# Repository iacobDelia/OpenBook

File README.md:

# Bill of Materials
| Componenta    | Link | Datasheet
| -------- | ------- |--------|
| ESP32_WROVER_EAGLE-LTSPICE_RR0402  | https://www.snapeda.com/parts/RC0402FR-07226RL/Yageo/view-part/    |https://www.snapeda.com/parts/RC0402FR-07226RL/Yageo/datasheet/
| QWIIC_CONNECTORJS-1MM | https://www.snapeda.com/parts/PRT-14417/SparkFun/view-part/     |https://www.snapeda.com/parts/PRT-14417/SparkFun%20Electronics/datasheet/
|BUTTON_CUSYOMV1|https://industry.panasonic.com/global/en/downloads?tab=cad&small_g_cd=203&part_no=EVQPUJ02K&q=RVZRUFVKMDJLJTdDMTMlN0MyMDMlN0MzNDU5JTdDMSU3QyU3QyU3Q2ZhbHNl|https://industry.panasonic.com/global/en/downloads?tab=catalog&small_g_cd=203&part_no=EVQPUJ02K&q=RVZRUFVKMDJLJTdDMTMlN0MyMDMlN0MzNDU5JTdDMSU3QyU3QzIlN0NmYWxzZQ%3D%3D
|ESP32_WROVER_EAGLE-LTSPICE_CC0402|https://componentsearchengine.com/part-view/CC0402MRX5R5BB106/YAGEO|https://componentsearchengine.com/Datasheets/2/CC0402MRX5R5BB106.pdf
|CPH3225A|https://www.snapeda.com/parts/CPH3225A/Seiko+Instruments/view-part/?ref=eda|https://www.snapeda.com/parts/CPH3225A/Seiko%20Instruments/datasheet/|
|ADAFRUIT_LEDCHIP-LED0603|https://www.snapeda.com/parts/KP-1608SURCK/Kingbright/view-part/?ref=search&t=LED%200603|https://www.snapeda.com/parts/KP-1608SURCK/Kingbright/datasheet/
|112A-TAAR-R03_ATTEND|https://store.comet.bg/en/Catalogue/Product/43497/|https://store.comet.bg/en/Catalogue/Product/43497/|
|744043680IND_4828-WE-TPC_WRE|https://www.digikey.sg/en/models/1638515|https://www.we-online.com/components/products/datasheet/744043680.pdf
|BD5229G-TR|https://componentsearchengine.com/part-view/BD5229G-TR/ROHM%20Semiconductor|https://datasheet.datasheetarchive.com/originals/distributors/Datasheets_SAMA/f2b9741ef86007909f138d561a359946.pdf|
|CPH3225A|https://www.snapeda.com/parts/CPH3225A/Seiko+Instruments/view-part/?ref=eda|https://www.snapeda.com/parts/CPH3225A/Seiko%20Instruments/datasheet/|
|DS3231SN|https://www.snapeda.com/parts/DS3231SN%23/Analog+Devices/view-part/?ref=eda|https://www.snapeda.com/parts/DS3231SN%23/Analog%20Devices/datasheet/|
|ESP32-C6-WROOM-1-N8|https://www.snapeda.com/parts/ESP32-C6-WROOM-1-N8/Espressif+Systems/view-part/?ref=eda|https://www.snapeda.com/parts/ESP32-C6-WROOM-1-N8/Espressif%20Systems/datasheet/
|MCP73831|https://www.digikey.com/en/models/1874108|https://ww1.microchip.com/downloads/aemDocuments/documents/APID/ProductDocuments/DataSheets/MCP73831-Family-Data-Sheet-DS20001984H.pdf|
|ESP32_WROVER_BME680_BME680|https://www.snapeda.com/parts/BME680/Bosch/view-part/?welcome=home|https://www.snapeda.com/parts/BME680/Bosch%20Sensortec/datasheet/|
|ESP32_WROVER_EAGLE-LTSPICE_CC0402|https://componentsearchengine.com/Datasheets/2/CC0402MRX5R5BB106.pdf|https://componentsearchengine.com/part-view/CC0402MRX5R5BB106/YAGEO|
|ESP32_WROVER_SPARKFUN-DISCRETESEMI_MOSFET_PCH-DMG2305UX-7|https://componentsearchengine.com/part-view/DMG2305UX-7/Diodes%20Incorporated|https://www.diodes.com//assets/Datasheets/DMG2305UX.pdf|
|ESP32C6_VARISTORCN1812|https://www.mouser.co.uk/ProductDetail/EPCOS-TDK/B72520T0350K062?qs=dEfas%2FXlABIszF52uu7vrg%3D%3D|https://www.tdk-electronics.tdk.com/inf/75/db/CTVS_14/Surge_protection_series.pdf|
|FH34SRJ-24S-0.5SH_99_|https://componentsearchengine.com/part-view/XC6220A331MR-G/Torex|https://product.torexsemi.com/system/files/series/xc6220.pdf|
|MAX17048G+T10|https://www.snapeda.com/parts/MAX17048G+T10/Analog+Devices/view-part/?ref=eda|https://www.snapeda.com/parts/MAX17048G+T10/Analog%20Devices/datasheet/|
|MBR0530|https://ro.mouser.com/ProductDetail/KYOCERA-AVX/SD0805S020S1R0?qs=jCA%252BPfw4LHbpkAoSnwrdjw%3D%3D|https://ro.mouser.com/datasheet/2/40/schottky-3165252.pdf|
|PGB1010603MR|https://www.snapeda.com/parts/PGB1010603MR/Littelfuse/view-part/?ref=eda|https://www.snapeda.com/parts/PGB1010603MR/Littelfuse%20Inc./datasheet/|
|RCL_CPOL-EUCT3528|https://ro.mouser.com/ProductDetail/Vishay-Sprague/TR3B106K025C1300?qs=jCGqFXxTmLdffnuDkXzk1g%3D%3D|https://www.vishay.com/docs/40080/tr3.pdf|
|SAMACSYS_PARTS_USB4110-GF-A|https://componentsearchengine.com/part-view/USB4110-GF-A/GCT%20(GLOBAL%20CONNECTOR%20TECHNOLOGY)|https://gct.co/files/drawings/usb4110.pdf|
|SI1308EDL-T1-GE3|https://componentsearchengine.com/part-view/SI1308EDL-T1-GE3/Vishay|https://componentsearchengine.com/Datasheets/1/SI1308EDL-T1-GE3.pdf|
|SJ|https://grabcad.com/library/solder-jumpers-1||
|USBLC6-2SC6Y|https://www.snapeda.com/parts/USBLC6-2SC6Y/STMicroelectronics/view-part/?ref=eda|https://www.snapeda.com/parts/USBLC6-2SC6Y/STMicroelectronics/datasheet/|
|W25Q512JVEIQ|https://www.snapeda.com/parts/W25Q512JVEIQ/Winbond+Electronics/view-part/?ref=eda|https://www.snapeda.com/parts/W25Q512JVEIQ/Winbond%20Electronics/datasheet/|
|XC6220A331MR-G|https://componentsearchengine.com/part-view/XC6220A331MR-G/Torex|https://product.torexsemi.com/system/files/series/xc6220.pdf|

# Functionalitati Hardware
## Microcontroller
Microcontroller principal: ESP32-C6-WROOM-1-N8

    Interfețe: UART, I²C, SPI, GPIO, ADC, PWM, USB 2.0

    Comunicare wireless: WiFi 6 (802.11ax), Bluetooth 5.0 Low Energy, Zigbee & Thread (prin IEEE 802.15.4)

    Memorie: 8 MB Flash

    Rol: Controler central ce gestionează comunicația cu toate perifericele și modulele externe. Este responsabil pentru achiziția de date, procesare și trimiterea lor către o interfață (de ex. server sau aplicație mobilă).

Ceas în timp real: DS3231SN

    Tip: RTC (Real-Time Clock) cu compensare termică

    Interfață: I²C

    Rol: Asigură măsurarea precisă a timpului, util pentru timestamp-ul datelor colectate de senzori.

Senzor de mediu: BME680

    Măsoară: Temperatură, presiune, umiditate și compuși organici volatili (VOC)

    Interfață: I²C (poate fi și SPI)

    Rol: Oferă date esențiale de mediu pentru aplicații IoT, monitorizare atmosferică etc.

### Managementul energiei
MCP73831

    Rol: Încărcător Li-Ion / Li-Po

    Interfață: Analogică, configurabilă prin rezistențe externe

    Caracteristici: Control al curentului de încărcare, protecții integrate

MAX17048G+T10

    Rol: Fuel Gauge IC

    Interfață: I²C

    Funcții: Măsoară tensiunea și estimează nivelul bateriei (SoC - state of charge)

Memorie externă: W25Q512JVEIQ

    Tip: NOR Flash, 512Mbit

    Interfață: SPI

    Rol: Stocare de date (loguri, configurări, firmware OTA)

Protecție și integritate electrică

    USBLC6-2SC6Y – Protecție ESD pentru liniile USB

    PGB1010603MR – Protecție împotriva descărcărilor electrostatice (ESD)

    SI1308EDL-T1-GE3 / DMG2305UX-7 – MOSFET pentru comutarea energiei sau protecție

    BD5229G-TR – Regulator LDO de 2.9V

    Varistor CN1812 (B72520T0350K062) – Protecție la supratensiuni

    Diodă Schottky (MBR0530) – Prevenirea curenților inversi

Conectivitate externă

    QWIIC_CONNECTORJS-1MM – Conector pentru I²C (QWIIC standard, modular, plug-and-play)

    SAMACSYS_PARTS_USB4110-GF-A – USB-C pentru alimentare și comunicare

    112A-TAAR-R03_ATTEND – Conector placă-la-placă

    SJ (Solder Jumpers) – Permite configurarea opțională a traseelor prin punți de lipit

Feedback vizual & control

    ADAFRUIT_LEDCHIP-LED0603 (KP-1608SURCK) – LED de status

    BUTTON_CUSYOMV1 (EVQPUJ02K) – Buton mecanic, folosit pentru reset, input de utilizator sau inițierea unei funcții

# Total consum
Componentă|	Consum tipic|
|-------|----------|
|ESP32-C6|	~130mA |
|BME680|	~3.1µA (low power)|	
|DS3231SN|	~200nA	|
|MAX17048|	~23µA	|
|MCP73831|	până la 500mA|	
|LED-uri|	~2-10mA	|

Total estimativ în mod activ: ~150-180mA

## Conexiuni componente la pini ESP32-C6
RTC – DS3231SN

    Interfață: I²C

    Pini ESP32-C6 folosiți:

        GPIO8 – I²C SDA

        GPIO9 – I²C SCL

    Motiv: GPIO8 și GPIO9 sunt frecvent utilizați pentru magistrala I²C pe ESP32-C6 deoarece pot fi configurate software și sunt ușor de accesat. SDA și SCL trebuie trase cu rezistențe de pull-up (tipic 4.7kΩ).

Senzor mediu – BME680

    Interfață: I²C (partajează magistrala cu DS3231)

    Pini ESP32-C6 folosiți:

        GPIO8 – SDA

        GPIO9 – SCL

    Motiv: Magistrala I²C permite conectarea în paralel a mai multor dispozitive, fiecare având adresă unică.

Fuel Gauge – MAX17048

    Interfață: I²C

    Pini: Aceeași magistrală I²C (GPIO8 & GPIO9)

    Motiv: MAX17048 are adresă I²C fixă, deci trebuie verificat să nu fie conflict cu celelalte două componente (nu e cazul aici).

Memorie externă – W25Q512JVEIQ

    Interfață: SPI

    Pini ESP32-C6:

        GPIO4 – SPI MOSI

        GPIO5 – SPI MISO

        GPIO6 – SPI CLK

        GPIO7 – SPI CS

    Motiv: Aceste GPIO-uri sunt pinii SPI hardware dedicați pe ESP32-C6 și asigură performanță maximă și compatibilitate cu interfața SPI (QSPI în cazul memoriei).

LED (KP-1608SURCK)

    Interfață: GPIO (digital out, cu rezistor în serie)

    Pin:

        GPIO3 – LED Control

    Motiv: GPIO3 este un pin liber cu capabilități PWM, ceea ce permite și control al intensității (dimming), nu doar on/off.

Buton (EVQPUJ02K)

    Interfață: GPIO + Pull-up intern

    Pin:

        GPIO0 – Buton utilizator

    Motiv: GPIO0 este adesea folosit și pentru bootloader/reset (cu atenție la stări în timpul pornirii). E un pin convenabil pentru input digital.

Qwiic Connector (I²C extensibil)

    Pini: I²C SDA/SCL partajați

        GPIO8 – SDA

        GPIO9 – SCL

    Motiv: Qwiic folosește același protocol I²C, deci toate dispozitivele compatibile Qwiic se pot lega în paralel la acești pini.

MCP73831 – Încărcare baterie

    Pini:

        VBUS / USB – Alimentare 5V

        STAT pin legat la GPIO10 (monitorizare charging status)

    Motiv: GPIO10 este configurabil ca input pentru a citi starea de încărcare (LED status al MCP73831 conectat la pinul STAT).

MAX17048 – Fuel Gauge

    Alimentare + I²C (vezi mai sus)

    INT (optional): Conectat la GPIO1

    Motiv: GPIO1 poate fi configurat cu întrerupere (interrupt) pentru notificări despre nivelul bateriei critic/scăzut.

USB4110-GF-A – USB-C connector

    Funcție: Alimentare 5V și comunicație

    Pin USB D+ / D- conectați la:

        GPIO18 – USB D+

        GPIO19 – USB D-

    Motiv: ESP32-C6 are suport USB nativ. Aceste GPIO-uri sunt default pentru perifericul USB Device.

Alte conexiuni:

    CPH3225A (oscilator 32.768 kHz) – utilizat pentru RTC, conectat la pinul dedicat RTC_CLKIN (sau la DS3231 dacă nu e folosit direct de MCU)

    MOSFET & diodă Schottky – control și protecție, comutarea pinilor GPIO pentru pornire/oprire module

    Varistor, rezistențe, condensatori – pasive pentru protecție, filtrare și stabilitate electrică (nu folosesc GPIO-uri direct)

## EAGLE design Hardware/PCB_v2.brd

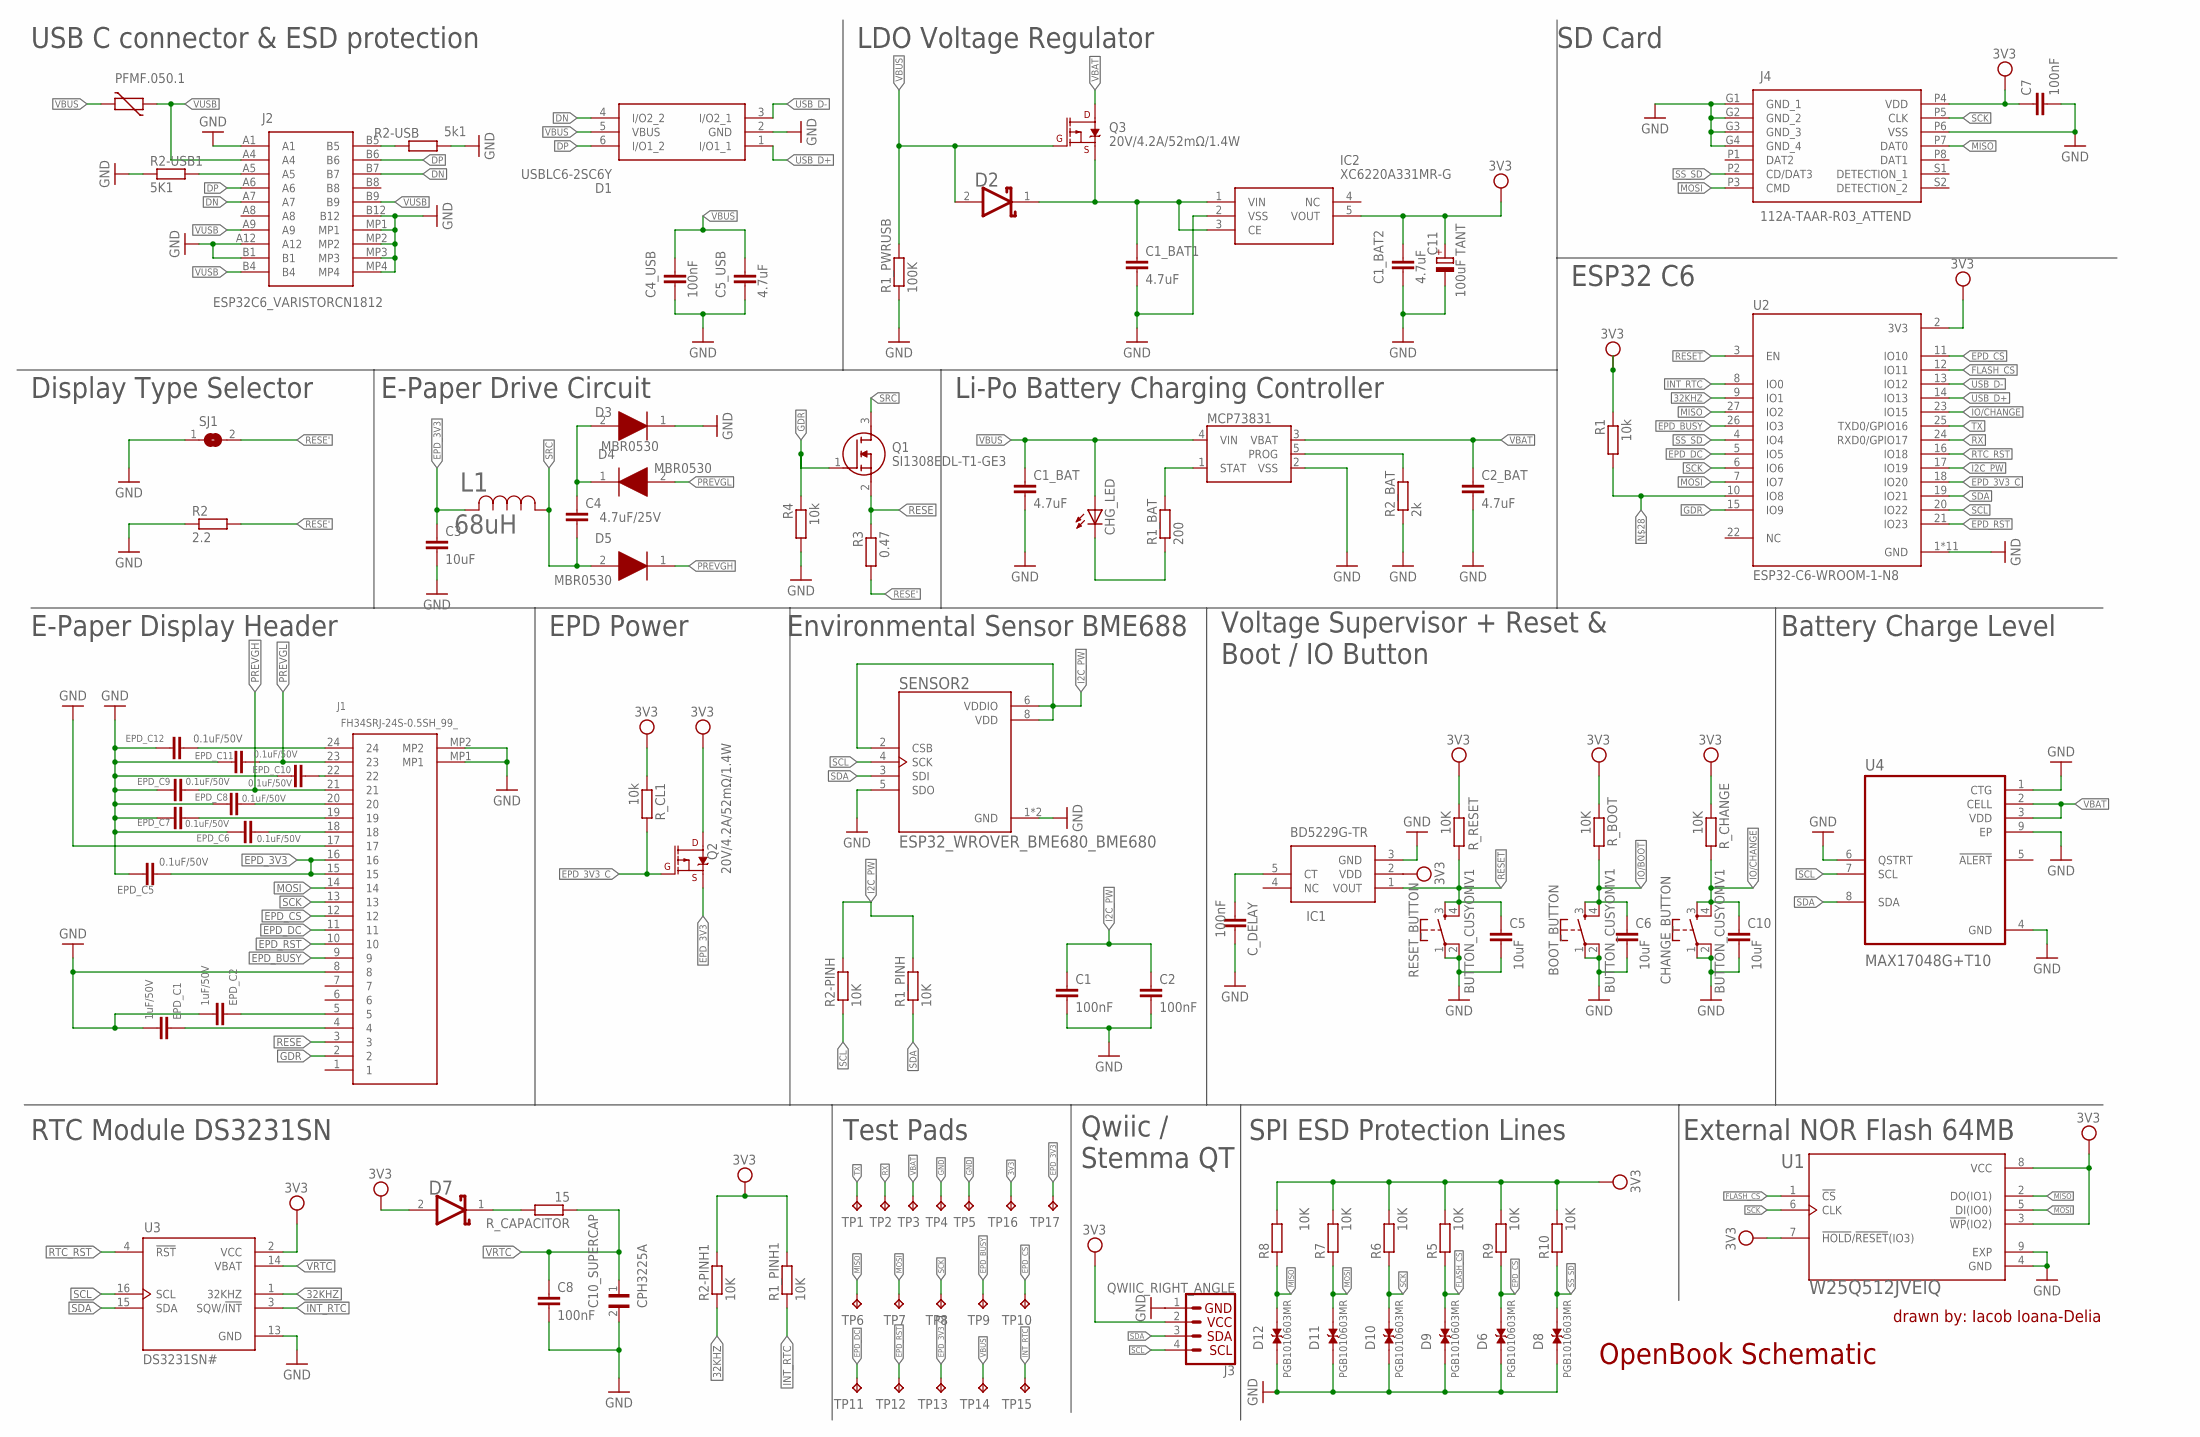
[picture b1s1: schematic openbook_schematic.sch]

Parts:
BOOT_BUTTON: BUTTON_CUSYOMV1; MYBUTTON
C1, C2, C4_USB, C7, C8: 100nF; ESP32_WROVER_EAGLE-LTSPICE_C0402
C1_BAT, C1_BAT1, C1_BAT2, C2_BAT, C5_USB: 4.7uF; ESP32_WROVER_EAGLE-LTSPICE_C0402
C3, C5, C6, C10: 10uF; ESP32_WROVER_EAGLE-LTSPICE_C0402
C4: 4.7uF/25V; ESP32_WROVER_EAGLE-LTSPICE_C0402
C10_SUPERCAP: CPH3225A; CAPCP3225X100N
C11: 100uF TANT; RCL_CT3528
CHANGE_BUTTON: BUTTON_CUSYOMV1; MYBUTTON
CHG_LED: ADAFRUIT_LEDCHIP-LED0603; ADAFRUIT_CHIP-LED0603
C_DELAY: 100nF; ESP32_WROVER_EAGLE-LTSPICE_C0402
D1: USBLC6-2SC6Y; SOT95P280X145-6N
D2, D7: ESP32_WROVER_AVX---SD0805S020S1R0_AVX_SD0805S020S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; ESP32_WROVER_AVX---SD0805S020S1R0_AVX_SD0805S020S1R0_0
D3, D4, D5: MBR0530; SOD3716X135N
D6, D8, D9, D10, D11, D12: PGB1010603MR; DIOC1608X36N
EPD_C1, EPD_C2: 1uF/50V; ESP32_WROVER_EAGLE-LTSPICE_C0402
EPD_C5, EPD_C6, EPD_C7, EPD_C8, EPD_C9, EPD_C10, EPD_C11, EPD_C12: 0.1uF/50V; ESP32_WROVER_EAGLE-LTSPICE_C0402
IC1: BD5229G-TR; SOT95P280X125-5N
IC2: XC6220A331MR-G; SOT95P280X120-5N
J1: FH34SRJ-24S-0.5SH_99_; FH34SRJ24S05SH99
J2: SAMACSYS_PARTS_USB4110-GF-A; SAMACSYS_PARTS_USB4110GFA
J3: QWIIC_RIGHT_ANGLE; JST04_1MM_RA
J4: 112A-TAAR-R03_ATTEND; 112ATAARR03ATTEND
L1: 68uH; IND_4828-WE-TPC_WRE
MCP73831: ESP32_WROVER_SPARKFUN-IC-POWER_MCP73831; ESP32_WROVER_SPARKFUN-IC-POWER_SOT23-5
PFMF.050.1: ESP32C6_VARISTORCN1812; ESP32C6_VARISTOR_CT/CN1812
Q1: SI1308EDL-T1-GE3; SOT65P210X110-3N
Q2, Q3: 20V/4.2A/52mΩ/1.4W; ESP32_WROVER_SPARKFUN-DISCRETESEMI_SOT23-3
R1, R4: 10k; ESP32_WROVER_EAGLE-LTSPICE_R0402
R1_BAT: 200; ESP32_WROVER_EAGLE-LTSPICE_R0402
R1_PINH, R1_PINH1, R2-PINH, R2-PINH1, R5, R6, R7, R8, R9, R10: 10K; ESP32_WROVER_EAGLE-LTSPICE_R0402
R1_PWRUSB: 100K; ESP32_WROVER_EAGLE-LTSPICE_R0402
R2: 2.2; ESP32_WROVER_EAGLE-LTSPICE_R0402
R2-USB: 5k1; ESP32_WROVER_EAGLE-LTSPICE_R0402
R2-USB1: 5K1; ESP32_WROVER_EAGLE-LTSPICE_R0402
R2_BAT: 2k; ESP32_WROVER_EAGLE-LTSPICE_R0402
R3: 0.47; ESP32_WROVER_EAGLE-LTSPICE_R0402
RESET_BUTTON: BUTTON_CUSYOMV1; MYBUTTON
R_BOOT: 10K; ESP32_WROVER_EAGLE-LTSPICE_R0402
R_CAPACITOR: 15; ESP32_WROVER_EAGLE-LTSPICE_R0402
R_CHANGE: 10K; ESP32_WROVER_EAGLE-LTSPICE_R0402
R_CL1: 10k; ESP32_WROVER_EAGLE-LTSPICE_R0402
R_RESET: 10K; ESP32_WROVER_EAGLE-LTSPICE_R0402
SENSOR2: ESP32_WROVER_BME680_BME680; ESP32_WROVER_BME680_PSON80P300X300X100-8N
SJ1: SJ
TP1, TP2, TP3, TP4, TP5, TP6, TP7, TP8, TP9, TP10, TP11, TP12, TP13, TP14, TP15, TP16, TP17: TPTP20R; TP20R
U1: W25Q512JVEIQ; SON127P600X800X80-9N
U2: ESP32-C6-WROOM-1-N8; XCVR_ESP32-C6-WROOM-1-N8
U3: DS3231SN#; SOIC127P1032X265-16N
U4: MAX17048G+T10; SON50P200X200X80-9N

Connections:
3V3: C1_BAT2.1, C7.1, C11.+, D7.2 (ANODE), IC1.2 (VDD), IC2.5 (VOUT), J3.2, J4.P4 (VDD), Q2.3 (D), R1.1, R1_PINH1.2, R2-PINH1.2, R5.2, R6.2, R7.2, R8.2, R9.2, R10.2, R_BOOT.1, R_CHANGE.1, R_CL1.1, R_RESET.1, TP16.TP, U1.3 (!WP!(IO2)), U1.7 (!HOLD!/!RESET!(IO3)), U1.8 (VCC), U2.2 (3V3), U3.2 (VCC)
32KHZ: R2-PINH1.1, U2.9 (IO1), U3.1 (32KHZ)
DN: D1.4 (I/O2_2), J2.A7, J2.B7
DP: D1.6 (I/O1_2), J2.A6, J2.B6
EPD_3V3: C3.1, EPD_C5.1, J1.15, J1.16, L1.2, Q2.2 (S), TP17.TP
EPD_3V3_C: Q2.1 (G), R_CL1.2, TP13.TP, U2.18 (IO20)
EPD_BUSY: J1.9, TP9.TP, U2.26 (IO3)
EPD_CS: D6.2, J1.12, R9.1, TP10.TP, U2.11 (IO10)
EPD_DC: J1.11, TP11.TP, U2.5 (IO5)
EPD_RST: J1.10, TP12.TP, U2.21 (IO23)
FLASH_CS: D9.2, R5.1, U1.1 (!CS), U2.12 (IO11)
GND: BOOT_BUTTON.1, BOOT_BUTTON.2, C1.2, C1_BAT.2, C1_BAT1.2, C1_BAT2.2, C2.2, C2_BAT.2, C3.2, C4_USB.2, C5.2, C5_USB.2, C6.2, C7.2, C8.2, C10.2, C10_SUPERCAP.2, C11.-, CHANGE_BUTTON.1, CHANGE_BUTTON.2, C_DELAY.2, D1.2 (GND), D3.1 (K), D6.1, D8.1, D9.1, D10.1, D11.1, D12.1, EPD_C1.2, EPD_C2.2, EPD_C5.2, EPD_C6.2, EPD_C7.2, EPD_C8.2, EPD_C9.2, EPD_C10.2, EPD_C11.2, EPD_C12.2, IC1.3 (GND), IC2.2 (VSS), J1.8, J1.17, J1.MP1, J1.MP2, J2.A1, J2.A12, J2.B1, J2.B12, J2.MP1, J2.MP2, J2.MP3, J2.MP4, J3.1, J4.G1 (GND_1), J4.G2 (GND_2), J4.G3 (GND_3), J4.G4 (GND_4), J4.P6 (VSS), MCP73831.2 (VSS), R1_PWRUSB.1, R2.1, R2-USB.2, R2-USB1.1, R2_BAT.1, R4.2, RESET_BUTTON.1, RESET_BUTTON.2, SENSOR2.1 (GND), SENSOR2.5 (SDO), SENSOR2.7 (GND), SJ1.1, TP4.TP, TP5.TP, U1.4 (GND), U1.9 (EXP), U2.1 (GND), U2.28 (GND), U2.29_1 (GND), U2.29_2 (GND), U2.29_3 (GND), U2.29_4 (GND), U2.29_5 (GND), U2.29_6 (GND), U2.29_7 (GND), U2.29_8 (GND), U2.29_9 (GND), U3.13 (GND), U4.1 (CTG), U4.4 (GND), U4.6 (QSTRT), U4.9 (EP)
I2C_PW: C1.1, C2.1, R1_PINH.2, R2-PINH.2, SENSOR2.2 (CSB), SENSOR2.6 (VDDIO), SENSOR2.8 (VDD), U2.17 (IO19)
INT_RTC: R1_PINH1.1, TP15.TP, U2.8 (IO0), U3.3 (SQW/!INT)
IO/CHANGE: C10.1, CHANGE_BUTTON.3, CHANGE_BUTTON.4, R_CHANGE.2, U2.23 (IO15)
MISO: D12.2, J4.P7 (DAT0), R8.1, TP6.TP, U1.2 (DO(IO1)), U2.27 (IO2)
MOSI: D11.2, J1.14, J4.P3 (CMD), R7.1, TP7.TP, U1.5 (DI(IO0)), U2.7 (IO7)
unnamed: EPD_C1.1, J1.4
unnamed: EPD_C2.1, J1.5
unnamed: D7.1 (CATHODE), R_CAPACITOR.2
unnamed: EPD_C6.1, J1.18
unnamed: EPD_C7.1, J1.19
unnamed: EPD_C8.1, J1.20
unnamed: C_DELAY.1, IC1.5 (CT)
unnamed: EPD_C10.1, J1.22
unnamed: C4.1, D3.2 (A), D4.1 (K)
unnamed: EPD_C12.1, J1.24
unnamed: J2.B5, R2-USB.1
unnamed: MCP73831.1 (STAT), R1_BAT.2
unnamed: CHG_LED.C, R1_BAT.1
unnamed: MCP73831.5 (PROG), R2_BAT.2
unnamed: C1_BAT1.1, D2.1 (CATHODE), IC2.1 (VIN), IC2.3 (CE), Q3.2 (S)
unnamed: J2.A5, R2-USB1.2
PREVGH: D5.1 (K), EPD_C9.1, J1.21
PREVGL: D4.2 (A), EPD_C11.1, J1.23
RESE: J1.3, Q1.2 (S), R3.1
RESE': R2.2, R3.2, SJ1.2
RESET: C5.1, IC1.1 (VOUT), RESET_BUTTON.3, RESET_BUTTON.4, R_RESET.2, U2.3 (EN)
RTC_RST: U2.16 (IO18), U3.4 (!RST)
RX: TP2.TP, U2.24 (RXD0/GPIO17)
SCK: D10.2, J1.13, J4.P5 (CLK), R6.1, TP8.TP, U1.6 (CLK), U2.6 (IO6)
SCL: J3.4, R2-PINH.1, SENSOR2.4 (SCK), U2.20 (IO22), U3.16 (SCL), U4.7 (SCL)
SDA: J3.3, R1_PINH.1, SENSOR2.3 (SDI), U2.19 (IO21), U3.15 (SDA), U4.8 (SDA)
SRC: C4.2, D5.2 (A), L1.1, Q1.3 (D)
SS_SD: D8.2, J4.P2 (CD/DAT3), R10.1, U2.4 (IO4)
TX: TP1.TP, U2.25 (TXD0/GPIO16)
USB_D+: D1.1 (I/O1_1), U2.14 (IO13)
USB_D-: D1.3 (I/O2_1), U2.13 (IO12)
VBAT: C2_BAT.1, MCP73831.3 (VBAT), Q3.3 (D), TP3.TP, U4.2 (CELL), U4.3 (VDD)
VBUS: C1_BAT.1, C4_USB.1, C5_USB.1, CHG_LED.A, D1.5 (VBUS), D2.2 (ANODE), MCP73831.4 (VIN), PFMF.050.1.2, Q3.1 (G), R1_PWRUSB.2, TP14.TP
VRTC: C8.1, C10_SUPERCAP.1, R_CAPACITOR.1, U3.14 (VBAT)
VUSB: J2.A4, J2.A9, J2.B4, J2.B9, PFMF.050.1.1

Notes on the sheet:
E-Paper Display Header
RTC Module DS3231SN
Test Pads
Qwiic / Stemma QT
SPI ESD Protection Lines
External NOR Flash 64MB
Battery Charge Level
Voltage Supervisor + Reset & Boot / IO Button
Environmental Sensor BME688
EPD Power
Display Type Selector
E-Paper Drive Circuit
Li-Po Battery Charging Controller
ESP32 C6
SD Card
LDO Voltage Regulator
USB C connector & ESD protection
OpenBook Schematic
drawn by: Iacob Ioana-Delia

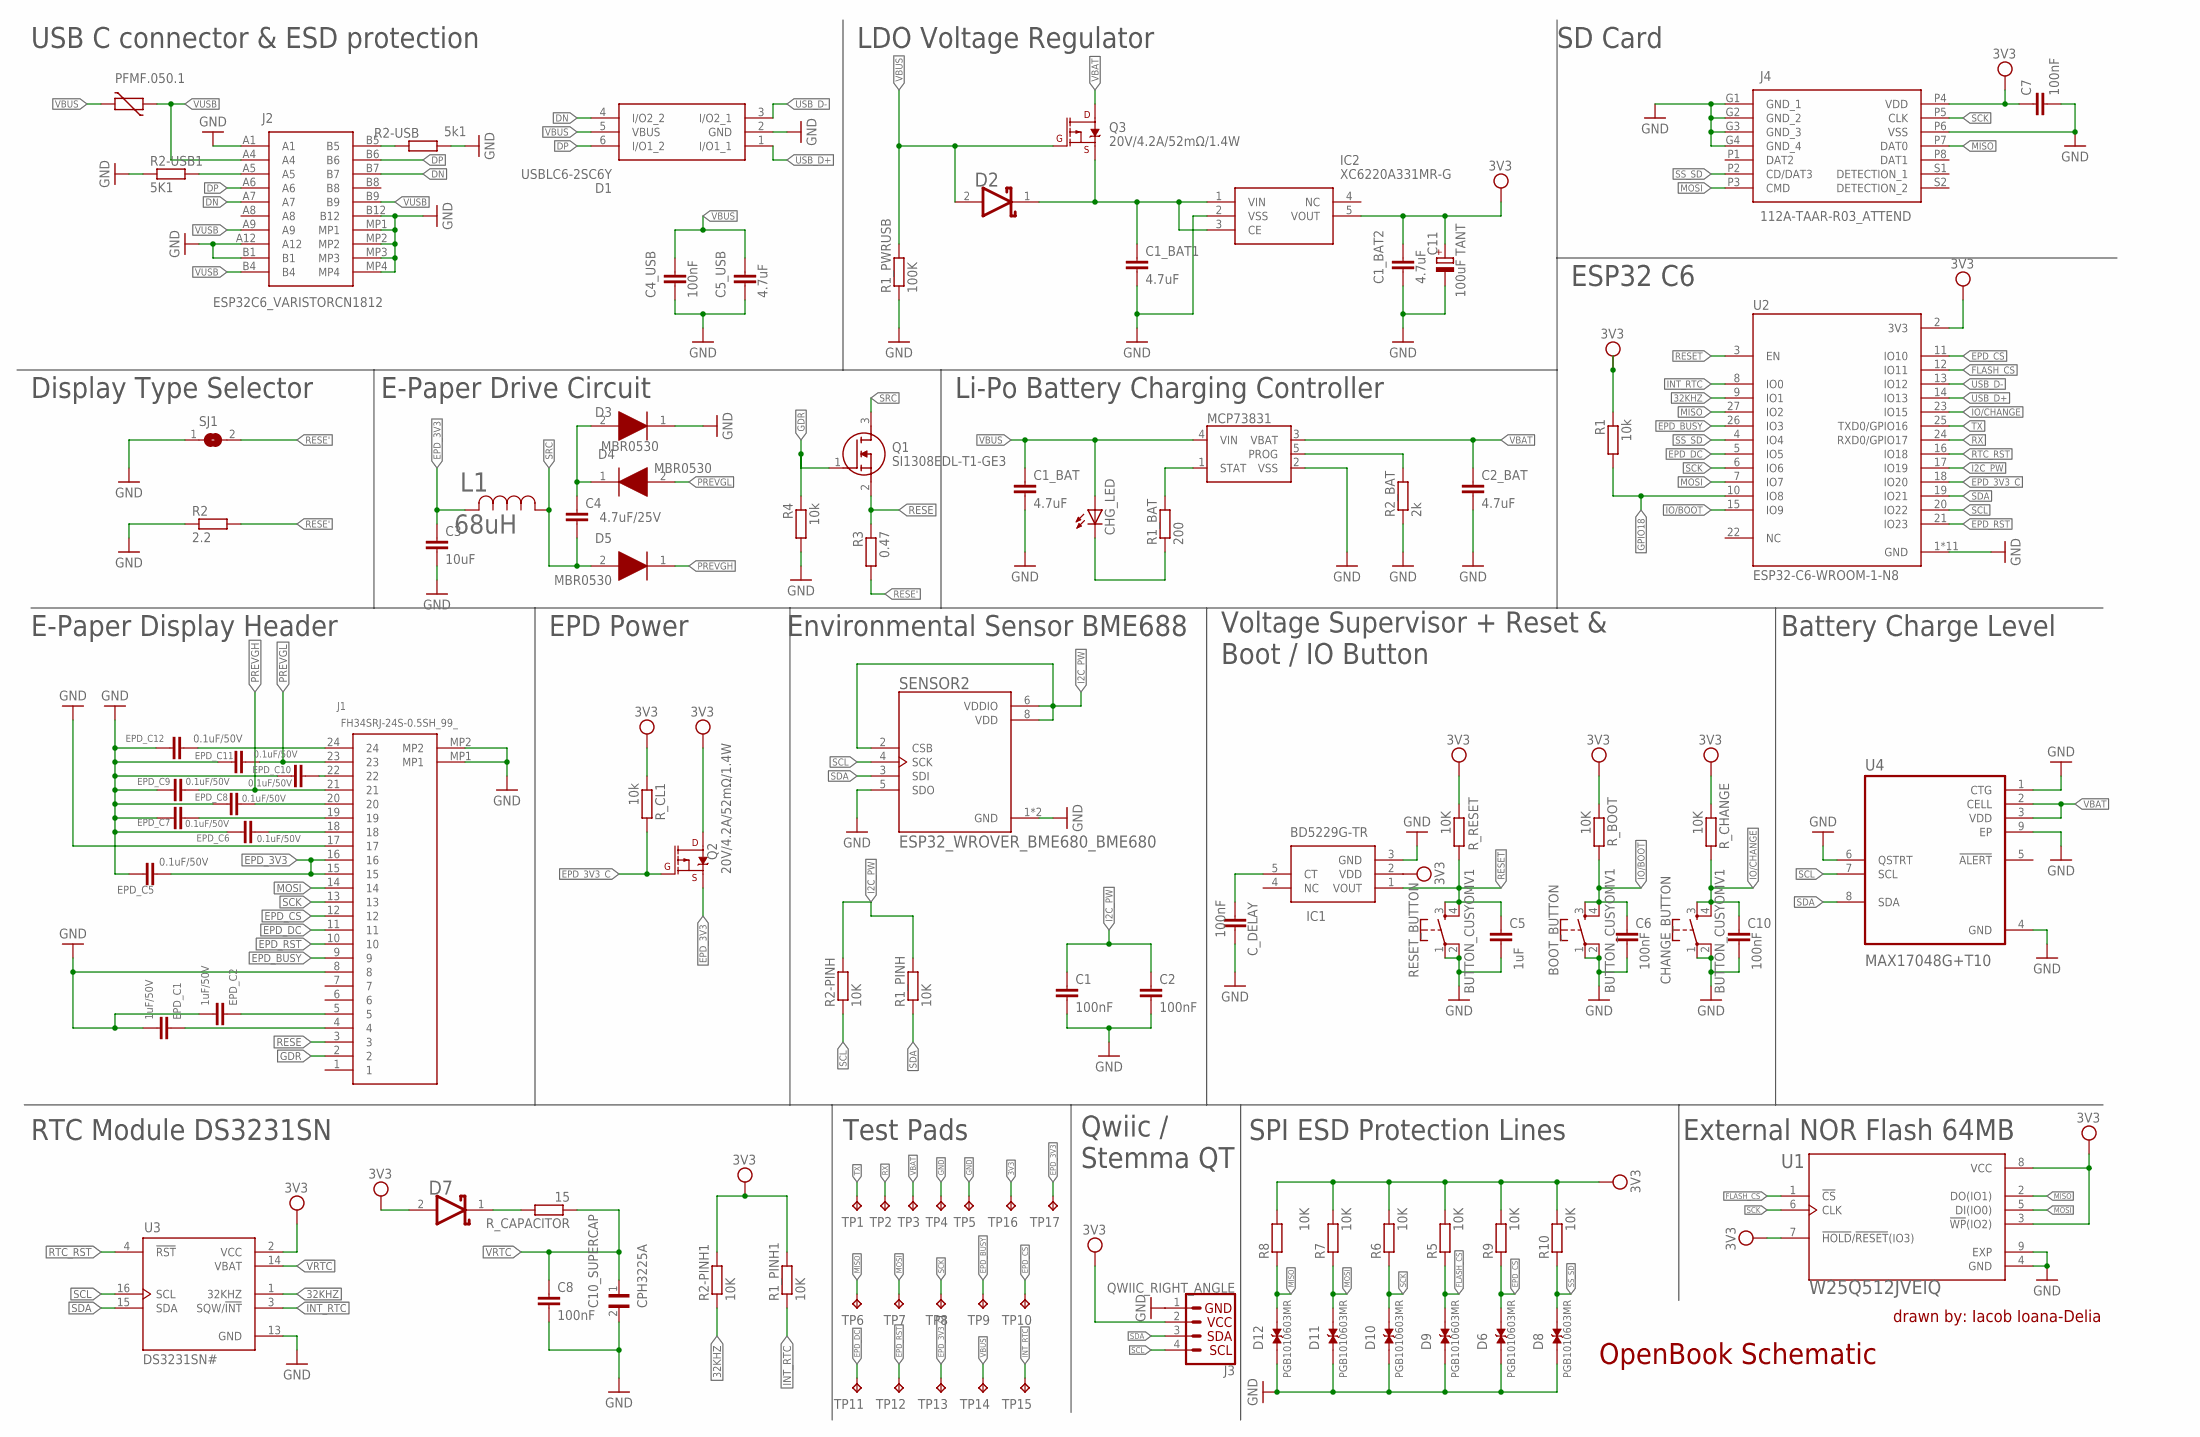
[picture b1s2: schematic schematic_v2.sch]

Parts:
BOOT_BUTTON: BUTTON_CUSYOMV1; MYBUTTON
C1, C2, C4_USB, C6, C7, C8, C10: 100nF; ESP32_WROVER_EAGLE-LTSPICE_C0402
C1_BAT, C1_BAT1, C1_BAT2, C2_BAT, C5_USB: 4.7uF; ESP32_WROVER_EAGLE-LTSPICE_C0402
C3: 10uF; ESP32_WROVER_EAGLE-LTSPICE_C0402
C4: 4.7uF/25V; ESP32_WROVER_EAGLE-LTSPICE_C0402
C5: 1uF; ESP32_WROVER_EAGLE-LTSPICE_C0402
C10_SUPERCAP: CPH3225A; CAPCP3225X100N
C11: 100uF TANT; RCL_CT3528
CHANGE_BUTTON: BUTTON_CUSYOMV1; MYBUTTON
CHG_LED: ADAFRUIT_LEDCHIP-LED0603; ADAFRUIT_CHIP-LED0603
C_DELAY: 100nF; ESP32_WROVER_EAGLE-LTSPICE_C0402
D1: USBLC6-2SC6Y; SOT95P280X145-6N
D2, D7: ESP32_WROVER_AVX---SD0805S020S1R0_AVX_SD0805S020S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; ESP32_WROVER_AVX---SD0805S020S1R0_AVX_SD0805S020S1R0_0
D3, D4, D5: MBR0530; SOD3716X135N
D6, D8, D9, D10, D11, D12: PGB1010603MR; DIOC1608X36N
EPD_C1, EPD_C2: 1uF/50V; ESP32_WROVER_EAGLE-LTSPICE_C0402
EPD_C5, EPD_C6, EPD_C7, EPD_C8, EPD_C9, EPD_C10, EPD_C11, EPD_C12: 0.1uF/50V; ESP32_WROVER_EAGLE-LTSPICE_C0402
IC1: BD5229G-TR; SOT95P280X125-5N
IC2: XC6220A331MR-G; SOT95P280X120-5N
J1: FH34SRJ-24S-0.5SH_99_; FH34SRJ24S05SH99
J2: SAMACSYS_PARTS_USB4110-GF-A; SAMACSYS_PARTS_USB4110GFA
J3: QWIIC_RIGHT_ANGLE; JST04_1MM_RA
J4: 112A-TAAR-R03_ATTEND; 112ATAARR03ATTEND
L1: 68uH; IND_4828-WE-TPC_WRE
MCP73831: ESP32_WROVER_SPARKFUN-IC-POWER_MCP73831; ESP32_WROVER_SPARKFUN-IC-POWER_SOT23-5
PFMF.050.1: ESP32C6_VARISTORCN1812; ESP32C6_VARISTOR_CT/CN1812
Q1: SI1308EDL-T1-GE3; SOT65P210X110-3N
Q2, Q3: 20V/4.2A/52mΩ/1.4W; ESP32_WROVER_SPARKFUN-DISCRETESEMI_SOT23-3
R1, R4: 10k; ESP32_WROVER_EAGLE-LTSPICE_R0402
R1_BAT: 200; ESP32_WROVER_EAGLE-LTSPICE_R0402
R1_PINH, R1_PINH1, R2-PINH, R2-PINH1, R5, R6, R7, R8, R9, R10: 10K; ESP32_WROVER_EAGLE-LTSPICE_R0402
R1_PWRUSB: 100K; ESP32_WROVER_EAGLE-LTSPICE_R0402
R2: 2.2; ESP32_WROVER_EAGLE-LTSPICE_R0402
R2-USB: 5k1; ESP32_WROVER_EAGLE-LTSPICE_R0402
R2-USB1: 5K1; ESP32_WROVER_EAGLE-LTSPICE_R0402
R2_BAT: 2k; ESP32_WROVER_EAGLE-LTSPICE_R0402
R3: 0.47; ESP32_WROVER_EAGLE-LTSPICE_R0402
RESET_BUTTON: BUTTON_CUSYOMV1; MYBUTTON
R_BOOT: 10K; ESP32_WROVER_EAGLE-LTSPICE_R0402
R_CAPACITOR: 15; ESP32_WROVER_EAGLE-LTSPICE_R0402
R_CHANGE: 10K; ESP32_WROVER_EAGLE-LTSPICE_R0402
R_CL1: 10k; ESP32_WROVER_EAGLE-LTSPICE_R0402
R_RESET: 10K; ESP32_WROVER_EAGLE-LTSPICE_R0402
SENSOR2: ESP32_WROVER_BME680_BME680; ESP32_WROVER_BME680_PSON80P300X300X100-8N
SJ1: SJ
TP1, TP2, TP3, TP4, TP5, TP6, TP7, TP8, TP9, TP10, TP11, TP12, TP13, TP14, TP15, TP16, TP17: TPTP20R; TP20R
U1: W25Q512JVEIQ; SON127P600X800X80-9N
U2: ESP32-C6-WROOM-1-N8; XCVR_ESP32-C6-WROOM-1-N8
U3: DS3231SN#; SOIC127P1032X265-16N
U4: MAX17048G+T10; SON50P200X200X80-9N

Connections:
3V3: C1_BAT2.1, C7.1, C11.+, D7.2 (ANODE), IC1.2 (VDD), IC2.5 (VOUT), J3.2, J4.P4 (VDD), Q2.3 (D), R1.1, R1_PINH1.2, R2-PINH1.2, R5.2, R6.2, R7.2, R8.2, R9.2, R10.2, R_BOOT.1, R_CHANGE.1, R_CL1.1, R_RESET.1, TP16.TP, U1.3 (!WP!(IO2)), U1.7 (!HOLD!/!RESET!(IO3)), U1.8 (VCC), U2.2 (3V3), U3.2 (VCC)
32KHZ: R2-PINH1.1, U2.9 (IO1), U3.1 (32KHZ)
DN: D1.4 (I/O2_2), J2.A7, J2.B7
DP: D1.6 (I/O1_2), J2.A6, J2.B6
EPD_3V3: C3.1, EPD_C5.1, J1.15, J1.16, L1.2, Q2.2 (S), TP17.TP
EPD_3V3_C: Q2.1 (G), R_CL1.2, TP13.TP, U2.18 (IO20)
EPD_BUSY: J1.9, TP9.TP, U2.26 (IO3)
EPD_CS: D6.2, J1.12, R9.1, TP10.TP, U2.11 (IO10)
EPD_DC: J1.11, TP11.TP, U2.5 (IO5)
EPD_RST: J1.10, TP12.TP, U2.21 (IO23)
FLASH_CS: D9.2, R5.1, U1.1 (!CS), U2.12 (IO11)
GND: BOOT_BUTTON.1, BOOT_BUTTON.2, C1.2, C1_BAT.2, C1_BAT1.2, C1_BAT2.2, C2.2, C2_BAT.2, C3.2, C4_USB.2, C5.2, C5_USB.2, C6.2, C7.2, C8.2, C10.2, C10_SUPERCAP.2, C11.-, CHANGE_BUTTON.1, CHANGE_BUTTON.2, C_DELAY.2, D1.2 (GND), D3.1 (K), D6.1, D8.1, D9.1, D10.1, D11.1, D12.1, EPD_C1.2, EPD_C2.2, EPD_C5.2, EPD_C6.2, EPD_C7.2, EPD_C8.2, EPD_C9.2, EPD_C10.2, EPD_C11.2, EPD_C12.2, IC1.3 (GND), IC2.2 (VSS), J1.8, J1.17, J1.MP1, J1.MP2, J2.A1, J2.A12, J2.B1, J2.B12, J2.MP1, J2.MP2, J2.MP3, J2.MP4, J3.1, J4.G1 (GND_1), J4.G2 (GND_2), J4.G3 (GND_3), J4.G4 (GND_4), J4.P6 (VSS), MCP73831.2 (VSS), R1_PWRUSB.1, R2.1, R2-USB.2, R2-USB1.1, R2_BAT.1, R4.2, RESET_BUTTON.1, RESET_BUTTON.2, SENSOR2.1 (GND), SENSOR2.5 (SDO), SENSOR2.7 (GND), SJ1.1, TP4.TP, TP5.TP, U1.4 (GND), U1.9 (EXP), U2.1 (GND), U2.28 (GND), U2.29_1 (GND), U2.29_2 (GND), U2.29_3 (GND), U2.29_4 (GND), U2.29_5 (GND), U2.29_6 (GND), U2.29_7 (GND), U2.29_8 (GND), U2.29_9 (GND), U3.13 (GND), U4.1 (CTG), U4.4 (GND), U4.6 (QSTRT), U4.9 (EP)
I2C_PW: C1.1, C2.1, R1_PINH.2, R2-PINH.2, SENSOR2.2 (CSB), SENSOR2.6 (VDDIO), SENSOR2.8 (VDD), U2.17 (IO19)
INT_RTC: R1_PINH1.1, TP15.TP, U2.8 (IO0), U3.3 (SQW/!INT)
IO/CHANGE: C10.1, CHANGE_BUTTON.3, CHANGE_BUTTON.4, R_CHANGE.2, U2.23 (IO15)
MISO: D12.2, J4.P7 (DAT0), R8.1, TP6.TP, U1.2 (DO(IO1)), U2.27 (IO2)
MOSI: D11.2, J1.14, J4.P3 (CMD), R7.1, TP7.TP, U1.5 (DI(IO0)), U2.7 (IO7)
unnamed: EPD_C1.1, J1.4
unnamed: EPD_C2.1, J1.5
unnamed: D7.1 (CATHODE), R_CAPACITOR.2
unnamed: EPD_C6.1, J1.18
unnamed: EPD_C7.1, J1.19
unnamed: EPD_C8.1, J1.20
unnamed: C_DELAY.1, IC1.5 (CT)
unnamed: EPD_C10.1, J1.22
unnamed: C4.1, D3.2 (A), D4.1 (K)
unnamed: EPD_C12.1, J1.24
unnamed: J2.B5, R2-USB.1
unnamed: MCP73831.1 (STAT), R1_BAT.2
unnamed: CHG_LED.C, R1_BAT.1
unnamed: MCP73831.5 (PROG), R2_BAT.2
unnamed: C1_BAT1.1, D2.1 (CATHODE), IC2.1 (VIN), IC2.3 (CE), Q3.2 (S)
unnamed: J2.A5, R2-USB1.2
PREVGH: D5.1 (K), EPD_C9.1, J1.21
PREVGL: D4.2 (A), EPD_C11.1, J1.23
RESE: J1.3, Q1.2 (S), R3.1
RESE': R2.2, R3.2, SJ1.2
RESET: C5.1, IC1.1 (VOUT), RESET_BUTTON.3, RESET_BUTTON.4, R_RESET.2, U2.3 (EN)
RTC_RST: U2.16 (IO18), U3.4 (!RST)
RX: TP2.TP, U2.24 (RXD0/GPIO17)
SCK: D10.2, J1.13, J4.P5 (CLK), R6.1, TP8.TP, U1.6 (CLK), U2.6 (IO6)
SCL: J3.4, R2-PINH.1, SENSOR2.4 (SCK), U2.20 (IO22), U3.16 (SCL), U4.7 (SCL)
SDA: J3.3, R1_PINH.1, SENSOR2.3 (SDI), U2.19 (IO21), U3.15 (SDA), U4.8 (SDA)
SRC: C4.2, D5.2 (A), L1.1, Q1.3 (D)
SS_SD: D8.2, J4.P2 (CD/DAT3), R10.1, U2.4 (IO4)
TX: TP1.TP, U2.25 (TXD0/GPIO16)
USB_D+: D1.1 (I/O1_1), U2.14 (IO13)
USB_D-: D1.3 (I/O2_1), U2.13 (IO12)
VBAT: C2_BAT.1, MCP73831.3 (VBAT), Q3.3 (D), TP3.TP, U4.2 (CELL), U4.3 (VDD)
VBUS: C1_BAT.1, C4_USB.1, C5_USB.1, CHG_LED.A, D1.5 (VBUS), D2.2 (ANODE), MCP73831.4 (VIN), PFMF.050.1.2, Q3.1 (G), R1_PWRUSB.2, TP14.TP
VRTC: C8.1, C10_SUPERCAP.1, R_CAPACITOR.1, U3.14 (VBAT)
VUSB: J2.A4, J2.A9, J2.B4, J2.B9, PFMF.050.1.1

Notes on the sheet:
E-Paper Display Header
RTC Module DS3231SN
Test Pads
Qwiic / Stemma QT
SPI ESD Protection Lines
External NOR Flash 64MB
Battery Charge Level
Voltage Supervisor + Reset & Boot / IO Button
Environmental Sensor BME688
EPD Power
Display Type Selector
E-Paper Drive Circuit
Li-Po Battery Charging Controller
ESP32 C6
SD Card
LDO Voltage Regulator
USB C connector & ESD protection
OpenBook Schematic
drawn by: Iacob Ioana-Delia

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
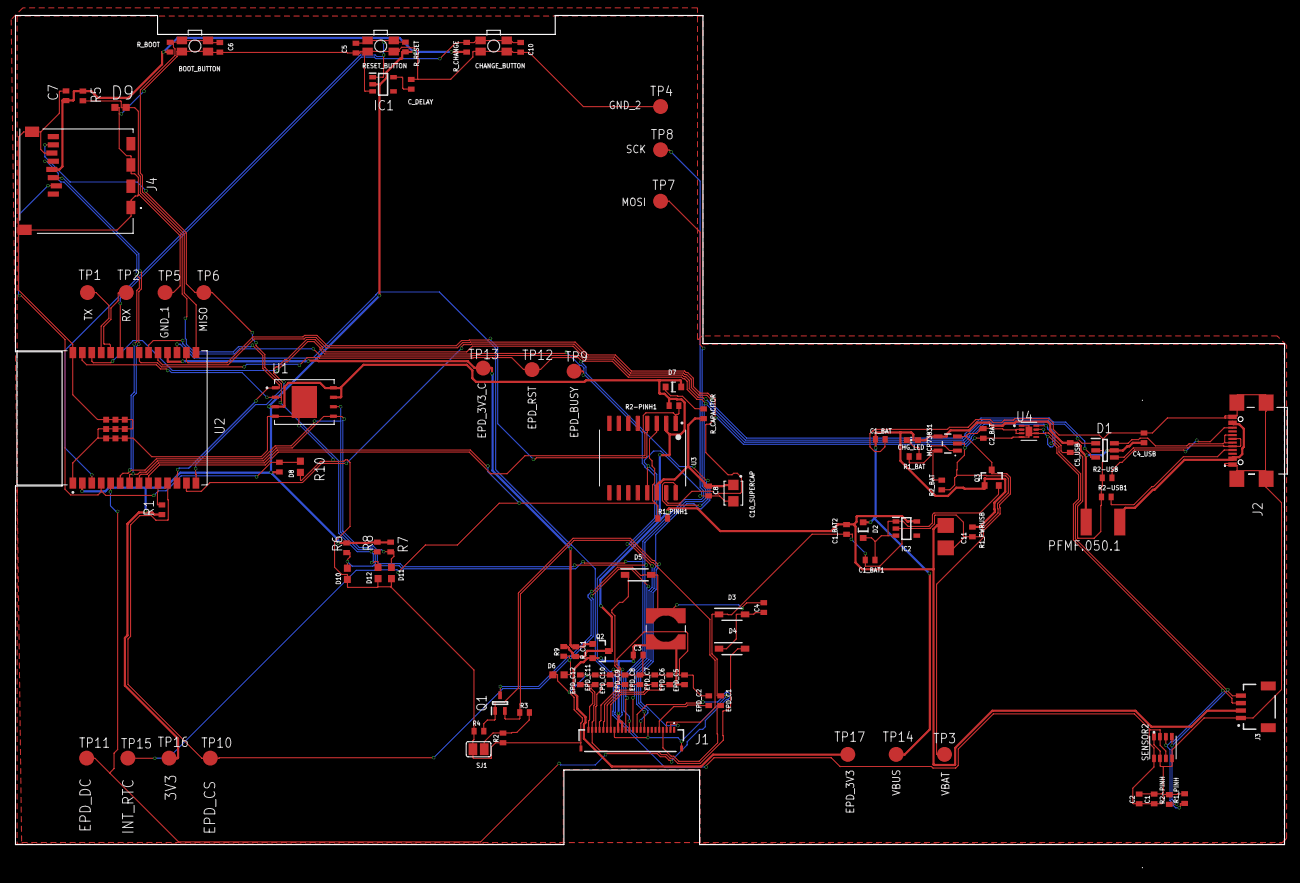
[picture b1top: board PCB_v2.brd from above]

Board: 2 copper layers, 170.2 x 114.3 mm, 103 parts (0 on the bottom side), 55 nets.

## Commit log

2025-04-11 Add new PCB and schematic files
    Solved the issues raised by bogdan1775. Mostly problems regarding to component name readability and polygon pour.

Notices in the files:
parts and their libraries:
COPYRIGHT: Copyright (C) 2024 Ultra Librarian. All rights reserved.
